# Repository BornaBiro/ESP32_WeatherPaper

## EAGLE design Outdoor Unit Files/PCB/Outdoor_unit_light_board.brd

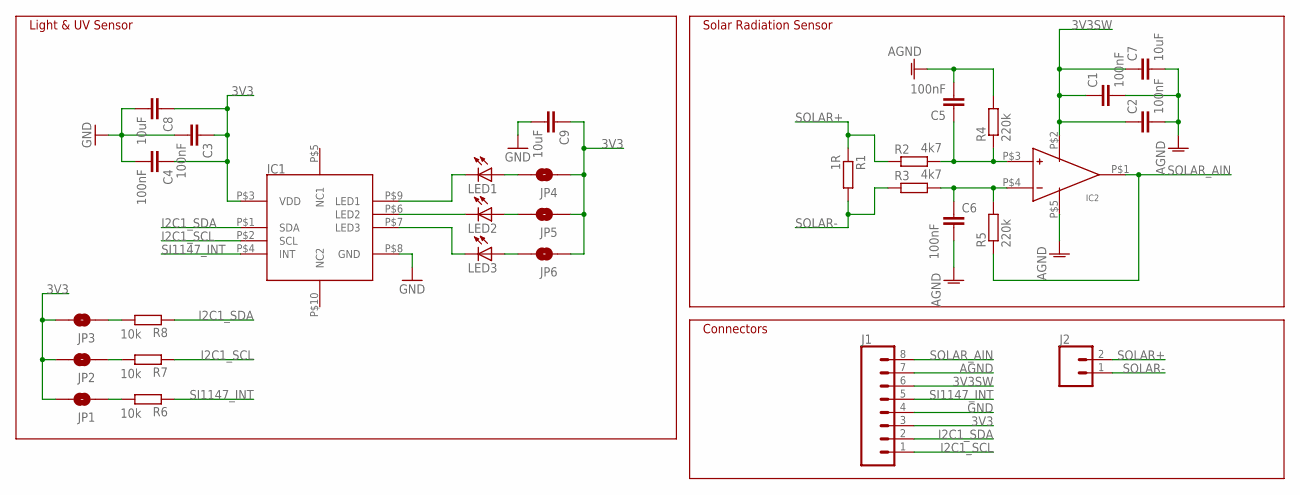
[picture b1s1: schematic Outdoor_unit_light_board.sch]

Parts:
C1, C2, C3, C4, C5, C6: 100nF; C0603K
C7, C8, C9: 10uF; C1206K
IC1: SI1147-A10-GMR; QFN10
IC2: MCP601RT-I/OT; SOT23-5
J1: CONN_08"; 1X08
J2: CONN_02; 1X02
JP1, JP2, JP3, JP4, JP5, JP6: JUMPER-SMT_2_NO_SILK; SMT-JUMPER_2_NO_SILK
LED1, LED2, LED3: LEDCHIPLED_0603; CHIPLED_0603
R1: 1R; R0603
R2, R3: 4k7; R0603
R4, R5: 220k; R0603
R6, R7, R8: 10k; R0603

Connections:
3V3: C3.1, C4.1, C8.1, C9.1, IC1.P$3 (VDD), J1.3, JP1.2, JP2.2, JP3.2, JP4.1, JP5.1, JP6.1
3V3SW: C1.1, C2.1, C7.1, IC2.P$2 (VDD), J1.6
AGND: C1.2, C2.2, C5.2, C6.2, C7.2, IC2.P$5 (VSS), J1.7, R4.2
GND: C3.2, C4.2, C8.2, C9.2, IC1.P$8 (GND), J1.4
I2C1_SCL: IC1.P$2 (SCL), J1.1, R7.1
I2C1_SDA: IC1.P$1 (SDA), J1.2, R8.1
unnamed: IC1.P$6 (LED2), LED2.C
unnamed: C5.1, IC2.P$3 (+IN), R2.2, R4.1
unnamed: C6.1, IC2.P$4 (-IN), R3.2, R5.2
unnamed: IC1.P$7 (LED3), LED3.C
unnamed: IC1.P$9 (LED1), LED1.C
unnamed: JP1.1, R6.2
unnamed: JP4.2, LED1.A
unnamed: JP5.2, LED2.A
unnamed: JP6.2, LED3.A
unnamed: JP2.1, R7.2
unnamed: JP3.1, R8.2
SI1147_INT: IC1.P$4 (INT), J1.5, R6.1
SOLAR+: J2.2, R1.1, R2.1
SOLAR-: J2.1, R1.2, R3.1
SOLAR_AIN: IC2.P$1 (OUT), J1.8, R5.1

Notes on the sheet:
Solar Radiation Sensor
Light & UV Sensor
Connectors

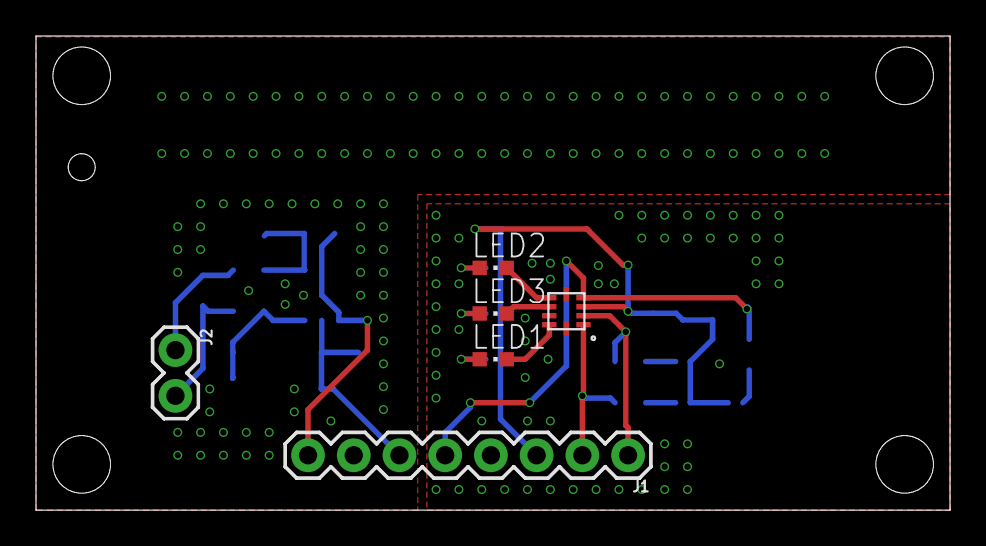
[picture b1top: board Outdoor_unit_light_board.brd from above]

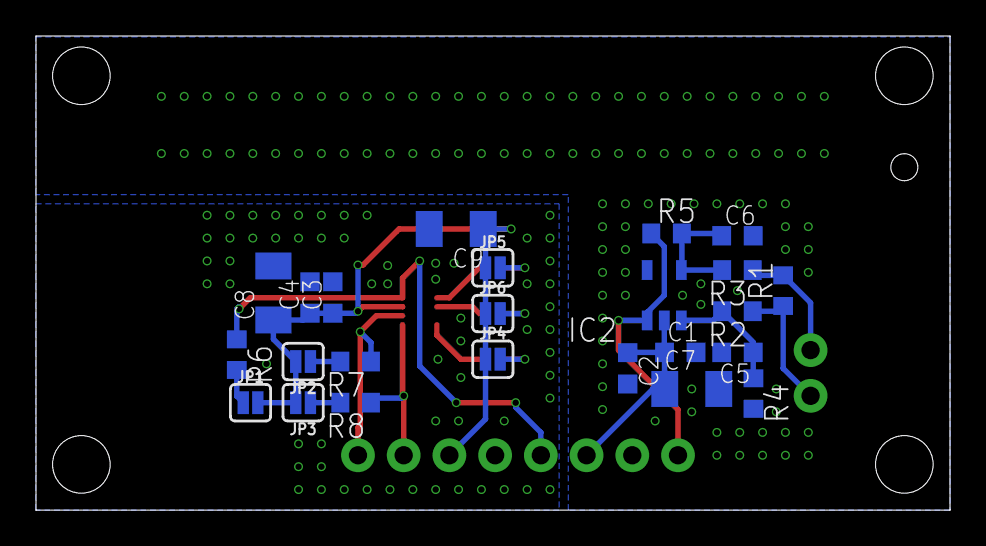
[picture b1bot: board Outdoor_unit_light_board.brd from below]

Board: 2 copper layers, 50.8 x 26.3 mm, 30 parts (24 on the bottom side), 21 nets.

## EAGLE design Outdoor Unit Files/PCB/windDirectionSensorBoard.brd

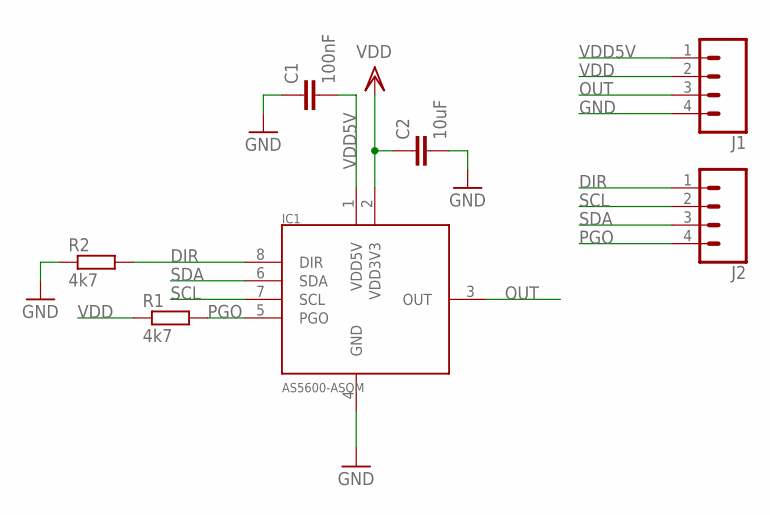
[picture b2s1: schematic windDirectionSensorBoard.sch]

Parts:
C1: 100nF; C0603K
C2: 10uF; C1206K
IC1: AS5600-ASOM; SOIC-8
J1, J2: CONN_04; 1X04
R1, R2: 4k7; R0603

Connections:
DIR: IC1.8 (DIR), J2.1, R2.2
GND: C1.1, C2.2, IC1.4 (GND), J1.4, R2.1
OUT: IC1.3 (OUT), J1.3
PGO: IC1.5 (PGO), J2.4, R1.2
SCL: IC1.7 (SCL), J2.2
SDA: IC1.6 (SDA), J2.3
VDD: C2.1, IC1.2 (VDD3V3), J1.2, R1.1
VDD5V: C1.2, IC1.1 (VDD5V), J1.1

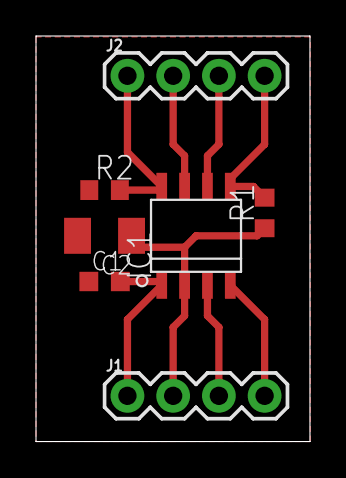
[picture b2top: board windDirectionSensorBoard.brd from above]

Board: 2 copper layers, 15.2 x 22.5 mm, 7 parts (0 on the bottom side), 8 nets.

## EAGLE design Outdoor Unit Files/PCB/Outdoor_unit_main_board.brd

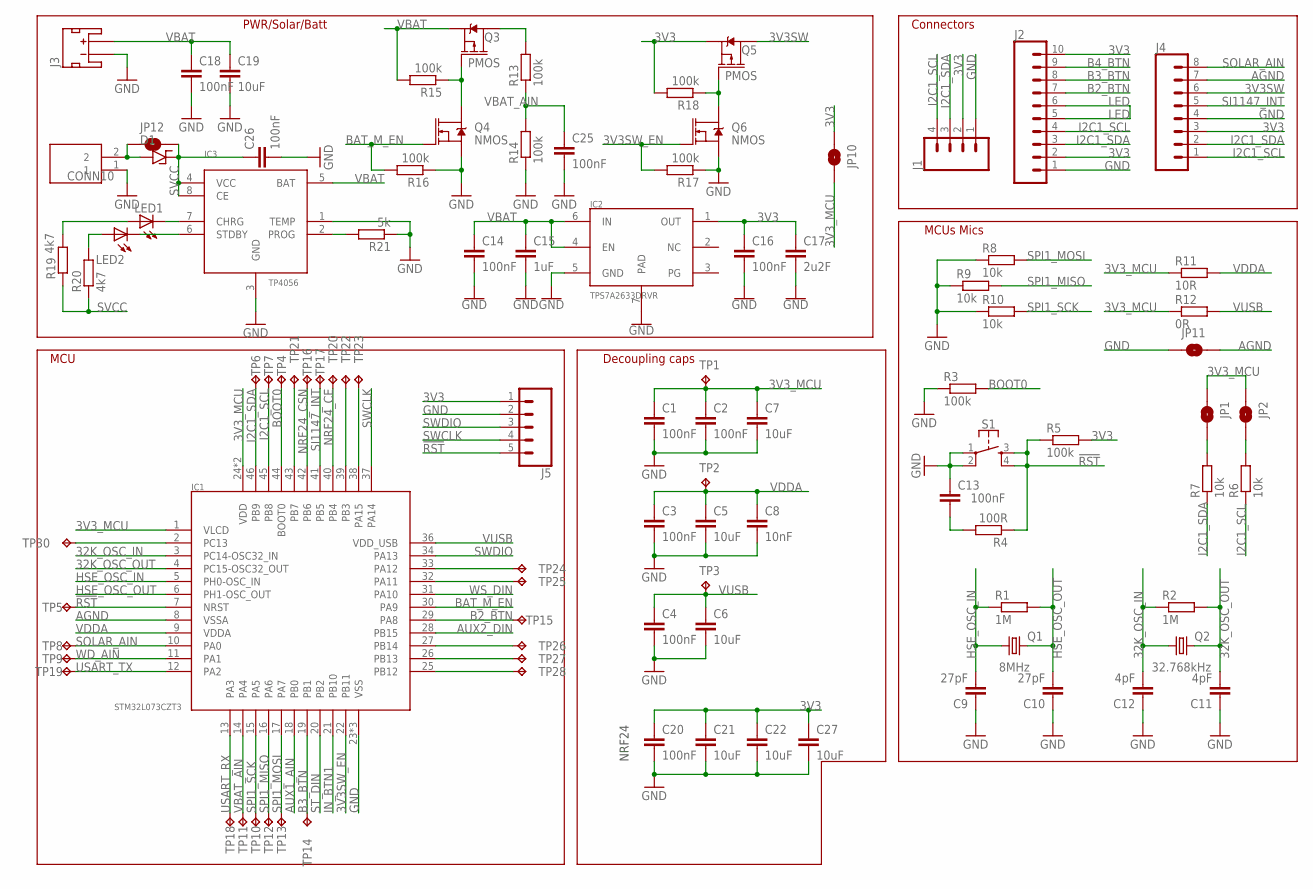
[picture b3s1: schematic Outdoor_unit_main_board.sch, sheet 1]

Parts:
C1, C2, C3, C4, C13, C14, C16, C18, C25, C26: 100nF; C0603K
C5, C6, C7, C19, C21, C22, C27: 10uF; C1206
C8: 10nF; C0603K
C9, C10: 27pF; C0603K
C11, C12: 4pF; C0603K
C15: 1uF; C0603K
C17: 2u2F; C0603K
C20: 100nF; C0603
CONN10: 1X02_SCREW_TERM; ASS_4091_CO
D1: SS24
IC1: STM32L073CZT3; LQFP-48
IC2: TPS7A2633DRVR; WSON-6
IC3: TP4056; SOP-8
J1: CONN_04; 1X04
J2: CONN_10"; 1X10
J3: JST_2MM_MALE; JST-2-SMD
J4: CONN_08"; 1X08
J5: CONN_05; 1X05
JP1, JP2, JP10, JP11, JP12: JUMPER-SMT_2_NO_SILK; SMT-JUMPER_2_NO_SILK
LED1, LED2: LEDCHIP-LED0805; CHIP-LED0805
Q1: 8MHz; HC49/S
Q2: 32.768kHz; TC26V
Q3, Q5: PMOS; SOT23-3
Q4, Q6: NMOS; SOT23-3
R1, R2: 1M; R0603
R3, R5, R13, R14, R15, R16, R17, R18: 100k; R0603
R4: 100R; R0603
R6, R7, R8, R9, R10: 10k; R0603
R11: 10R; R0603
R12: 0R; R0603
R19, R20: 4k7; R0603
R21: 5k; R0603
S1: MOMENTARY-SWITCH-SPST-2-SMD-5.2MM; TACTILE_SWITCH_SMD_5.2MM
TP1, TP2, TP3, TP4, TP5, TP6, TP7, TP8, TP9, TP10, TP11, TP12, TP13, TP14, TP15, TP16, TP17, TP18, TP19, TP20, TP21, TP22, TP23, TP24, TP25, TP26, TP27, TP28, TP30: TPTP15R; TP15R

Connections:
3V3: C16.1, C17.1, C20.1, C21.1, C22.1, C27.1, IC2.1 (OUT), J1.2, J2.2, J2.10, J4.3, J5.1, JP10.1, Q5.2 (S), R5.2, R18.2; also elsewhere on the board
3V3SW: J4.6, Q5.3 (D); also elsewhere on the board
3V3SW_EN: IC1.22 (PB11), Q6.1 (G), R17.2
3V3_MCU: C1.1, C2.1, C7.1, IC1.1 (VLCD), IC1.24 (VDD), IC1.48 (VDD), JP1.1, JP2.1, JP10.2, R11.1, R12.1, TP1.TP
32K_OSC_IN: C12.2, IC1.3 (PC14-OSC32_IN), Q2.1, R2.1
32K_OSC_OUT: C11.2, IC1.4 (PC15-OSC32_OUT), Q2.2, R2.2
!RST: IC1.7 (NRST), J5.5, R4.1, R5.1, S1.3, S1.4, TP5.TP
AGND: IC1.8 (VSSA), J4.7, JP11.2; also elsewhere on the board
AUX1_AIN: IC1.18 (PB0); also elsewhere on the board
AUX2_DIN: IC1.28 (PB15); also elsewhere on the board
B2_BTN: IC1.29 (PA8), J2.7, TP15.TP
B3_BTN: IC1.19 (PB1), J2.8, TP14.TP
B4_BTN: J2.9
BAT_M_EN: IC1.30 (PA9), Q4.1 (G), R16.2
BOOT0: IC1.44 (BOOT0), R3.2, TP4.TP
GND: C1.2, C2.2, C3.2, C4.2, C5.2, C6.2, C7.2, C8.2, C9.1, C10.1, C11.1, C12.1, C13.1, C14.2, C15.2, C16.2, C17.2, C18.2, C19.2, C20.2, C21.2, C22.2, C25.2, C26.2, C27.2, CONN10.1, IC1.23 (VSS), IC1.35 (VSS), IC1.47 (VSS), IC2.5 (GND), IC2.7 (PAD), IC3.1 (TEMP), IC3.3 (GND), J1.1, J2.1, J3.1 (-), J4.4, J5.2, JP11.1, Q4.2 (S), Q6.2 (S), R3.1, R8.1, R9.1, R10.1, R14.1, R16.1, R17.1, R21.1, S1.1, S1.2; also elsewhere on the board
HSE_OSC_IN: C9.2, IC1.5 (PH0-OSC_IN), Q1.1, R1.1
HSE_OSC_OUT: C10.2, IC1.6 (PH1-OSC_OUT), Q1.2, R1.2
I2C1_SCL: IC1.45 (PB8), J1.4, J2.4, J4.1, R6.1, TP7.TP; also elsewhere on the board
I2C1_SDA: IC1.46 (PB9), J1.3, J2.3, J4.2, R7.1, TP6.TP; also elsewhere on the board
IN_BTN1: IC1.21 (PB10); also elsewhere on the board
LED: J2.5, J2.6
unnamed: CONN10.2, D1.A, JP12.1
unnamed: JP1.2, R7.2
unnamed: C13.2, R4.2
unnamed: JP2.2, R6.2
unnamed: IC3.7 (CHRG), LED1.C
unnamed: IC3.6 (STDBY), LED2.C
unnamed: LED2.A, R20.2
unnamed: IC1.33 (PA12), TP24.TP
unnamed: IC1.32 (PA11), TP25.TP
unnamed: IC1.27 (PB14), TP26.TP
unnamed: IC1.26 (PB13), TP27.TP
unnamed: IC1.25 (PB12), TP28.TP
unnamed: IC1.38 (PA15), TP23.TP
unnamed: IC1.39 (PB3), TP22.TP
unnamed: IC1.43 (PB7), TP21.TP
unnamed: IC1.2 (PC13), TP30.TP
unnamed: Q3.3 (D), R13.2
unnamed: LED1.A, R19.2
unnamed: IC3.2 (PROG), R21.2
unnamed: Q3.1 (G), Q4.3 (D), R15.1
unnamed: Q5.1 (G), Q6.3 (D), R18.1
NRF24_CE: IC1.40 (PB4), TP20.TP; also elsewhere on the board
NRF24_CSN: IC1.42 (PB6), TP16.TP; also elsewhere on the board
SI1147_INT: IC1.41 (PB5), J4.5, TP17.TP
SOLAR_AIN: IC1.10 (PA0), J4.8, TP8.TP
SPI1_MISO: IC1.16 (PA6), R9.2, TP12.TP; also elsewhere on the board
SPI1_MOSI: IC1.17 (PA7), R8.2, TP13.TP; also elsewhere on the board
SPI1_SCK: IC1.15 (PA5), R10.2, TP10.TP; also elsewhere on the board
ST_DIN: IC1.20 (PB2); also elsewhere on the board
SVCC: C26.1, D1.C, IC3.4 (VCC), IC3.8 (CE), JP12.2, R19.1, R20.1
SWCLK: IC1.37 (PA14), J5.4
SWDIO: IC1.34 (PA13), J5.3
USART_RX: IC1.13 (PA3), TP18.TP
USART_TX: IC1.12 (PA2), TP19.TP
VBAT: C14.1, C15.1, C18.1, C19.1, IC2.4 (EN), IC2.6 (IN), IC3.5 (BAT), J3.2 (+), Q3.2 (S), R15.2
VBAT_AIN: C25.1, IC1.14 (PA4), R13.1, R14.2, TP11.TP
VDDA: C3.1, C5.1, C8.1, IC1.9 (VDDA), R11.2, TP2.TP
VUSB: C4.1, C6.1, IC1.36 (VDD_USB), R12.2, TP3.TP
WD_AIN: IC1.11 (PA1), TP9.TP; also elsewhere on the board
WS_DIN: IC1.31 (PA10); also elsewhere on the board

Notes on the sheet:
MCU
Decoupling caps
MCUs Mics
NRF24
PWR/Solar/Batt
Connectors

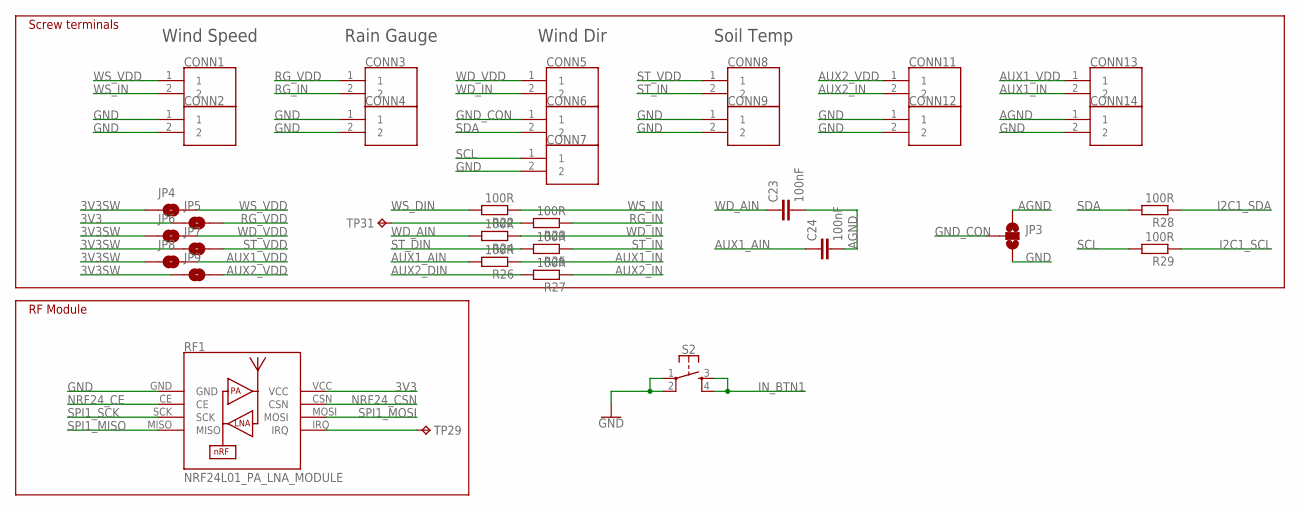
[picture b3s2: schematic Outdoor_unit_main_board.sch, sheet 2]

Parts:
C23, C24: 100nF; C0603K
CONN1, CONN2, CONN3, CONN4, CONN5, CONN6, CONN7, CONN8, CONN9, CONN11, CONN12, CONN13, CONN14: 1X02_SCREW_TERM; ASS_4091_CO
JP3: JUMPER-SMT_3_NO_SILK; SMT-JUMPER_3_NO_SILK
JP4, JP5, JP6, JP7, JP8, JP9: JUMPER-SMT_2_NO_SILK; SMT-JUMPER_2_NO_SILK
R22, R23, R24, R25, R26, R27, R28, R29: 100R; R0603
RF1: NRF24L01_PA_LNA_MODULE; NRF24L01_PA_LNA
S2: MOMENTARY-SWITCH-SPST-2-SMD-5.2MM; TACTILE_SWITCH_SMD_5.2MM
TP29, TP31: TPTP15R; TP15R

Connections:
3V3: JP5.1, RF1.VCC; also elsewhere on the board
3V3SW: JP4.1, JP6.1, JP7.1, JP8.1, JP9.1; also elsewhere on the board
AGND: C23.2, C24.2, CONN14.1, JP3.1; also elsewhere on the board
AUX1_AIN: C24.1, R26.2; also elsewhere on the board
AUX1_IN: CONN13.2, R26.1
AUX1_VDD: CONN13.1, JP8.2
AUX2_DIN: R27.2; also elsewhere on the board
AUX2_IN: CONN11.2, R27.1
AUX2_VDD: CONN11.1, JP9.2
GND: CONN2.1, CONN2.2, CONN4.1, CONN4.2, CONN7.2, CONN9.1, CONN9.2, CONN12.1, CONN12.2, CONN14.2, JP3.3, RF1.GND, S2.1, S2.2; also elsewhere on the board
GND_CON: CONN6.1, JP3.2
I2C1_SCL: R29.1; also elsewhere on the board
I2C1_SDA: R28.1; also elsewhere on the board
IN_BTN1: S2.3, S2.4; also elsewhere on the board
unnamed: RF1.IRQ, TP29.TP
unnamed: R23.2, TP31.TP
NRF24_CE: RF1.CE; also elsewhere on the board
NRF24_CSN: RF1.CSN; also elsewhere on the board
RG_IN: CONN3.2, R23.1
RG_VDD: CONN3.1, JP5.2
SCL: CONN7.1, R29.2
SDA: CONN6.2, R28.2
SPI1_MISO: RF1.MISO; also elsewhere on the board
SPI1_MOSI: RF1.MOSI; also elsewhere on the board
SPI1_SCK: RF1.SCK; also elsewhere on the board
ST_DIN: R25.2; also elsewhere on the board
ST_IN: CONN8.2, R25.1
ST_VDD: CONN8.1, JP7.2
WD_AIN: C23.1, R24.2; also elsewhere on the board
WD_IN: CONN5.2, R24.1
WD_VDD: CONN5.1, JP6.2
WS_DIN: R22.2; also elsewhere on the board
WS_IN: CONN1.2, R22.1
WS_VDD: CONN1.1, JP4.2

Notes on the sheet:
Wind Speed
Rain Gauge
Wind Dir
Soil Temp
Screw terminals
RF Module

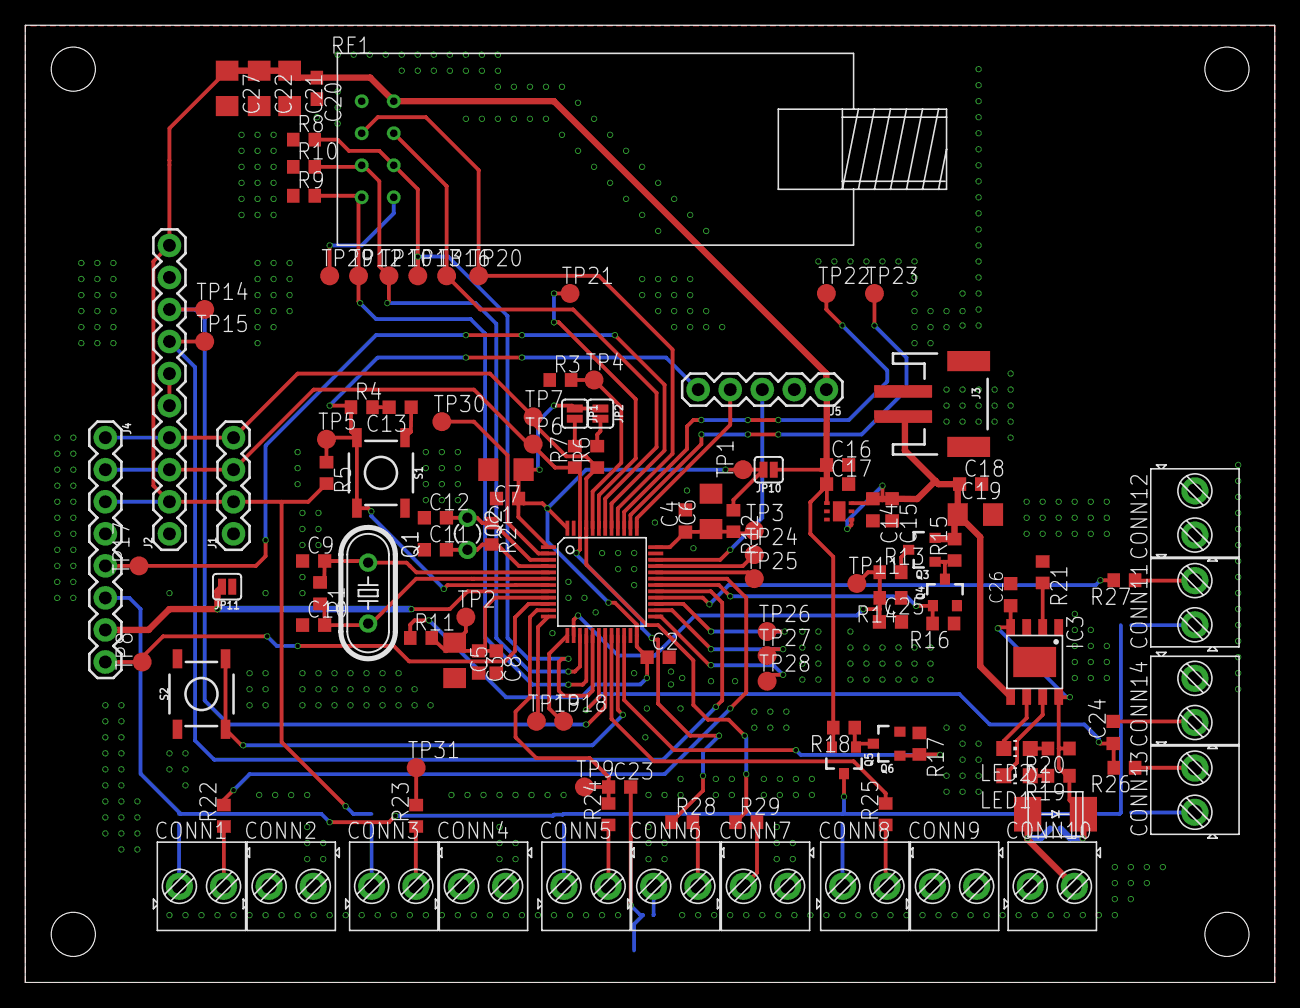
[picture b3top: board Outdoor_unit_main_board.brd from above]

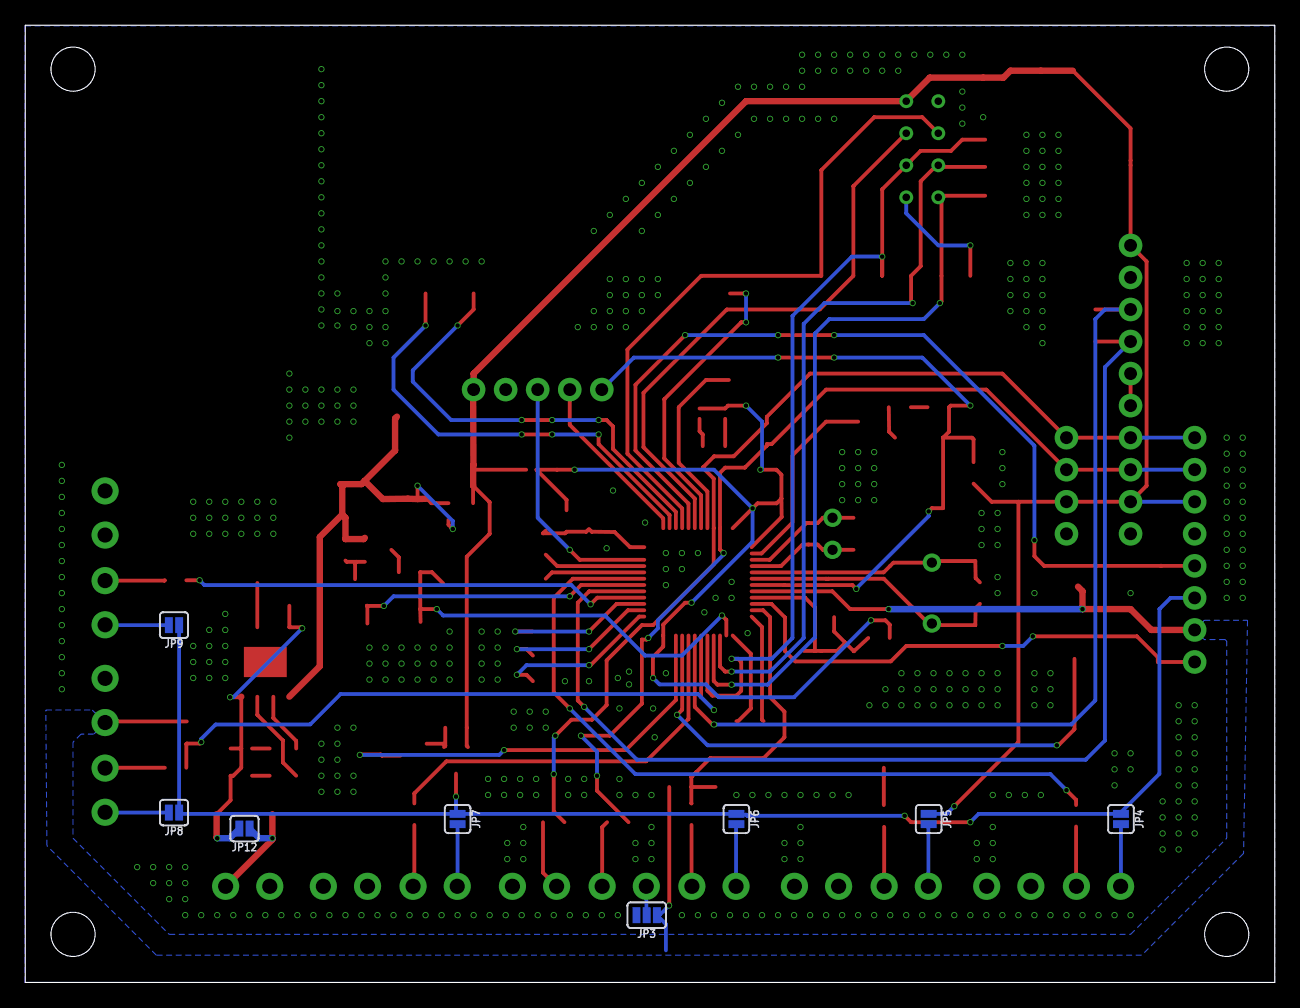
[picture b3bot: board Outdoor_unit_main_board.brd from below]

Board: 2 copper layers, 99.0 x 75.9 mm, 133 parts (8 on the bottom side), 78 nets.

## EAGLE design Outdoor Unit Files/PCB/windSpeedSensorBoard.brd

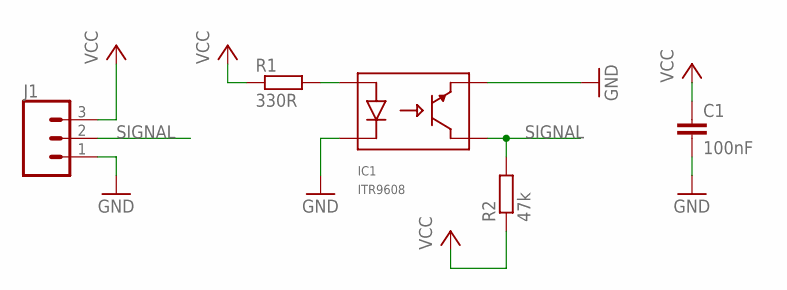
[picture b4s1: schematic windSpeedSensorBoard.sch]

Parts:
C1: 100nF; C0603K
IC1: ITR9608
J1: CONN_03; 1X03
R1: 330R; R0603
R2: 47k; R0603

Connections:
GND: C1.2, IC1.E, IC1.K, J1.1
unnamed: IC1.A, R1.2
SIGNAL: IC1.C, J1.2, R2.2
VCC: C1.1, J1.3, R1.1, R2.1

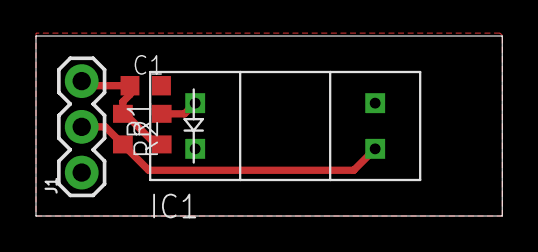
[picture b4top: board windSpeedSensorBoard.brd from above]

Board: 2 copper layers, 25.9 x 10.0 mm, 5 parts (0 on the bottom side), 4 nets.

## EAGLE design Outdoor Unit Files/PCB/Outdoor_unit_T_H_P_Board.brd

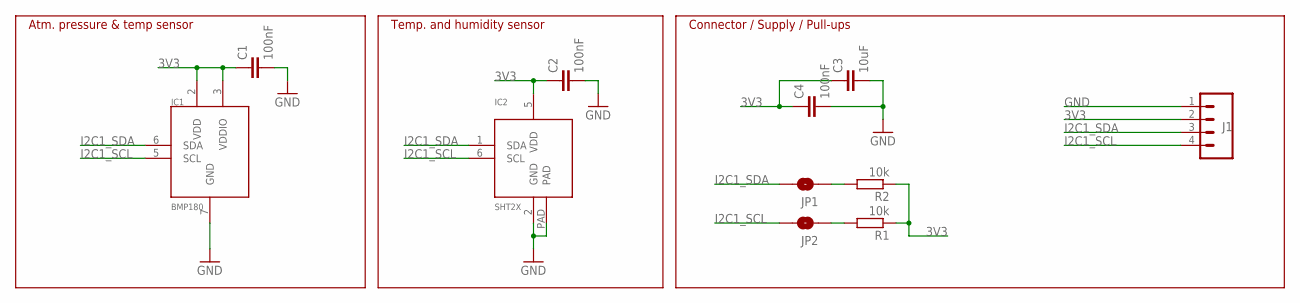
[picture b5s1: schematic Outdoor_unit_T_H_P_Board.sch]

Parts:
C1, C2, C4: 100nF; C0603K
C3: 10uF; C1206K
IC1: BMP180
IC2: SHT2X
J1: CONN_04; 1X04
JP1, JP2: JUMPER-SMT_2_NO_SILK; SMT-JUMPER_2_NO_SILK
R1, R2: 10k; R0603

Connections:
3V3: C1.1, C2.1, C3.1, C4.1, IC1.2 (VDD), IC1.3 (VDDIO), IC2.5 (VDD), J1.2, R1.1, R2.1
GND: C1.2, C2.2, C3.2, C4.2, IC1.7 (GND), IC2.2 (GND), IC2.PAD, J1.1
I2C1_SCL: IC1.5 (SCL), IC2.6 (SCL), J1.4, JP2.2
I2C1_SDA: IC1.6 (SDA), IC2.1 (SDA), J1.3, JP1.2
unnamed: JP2.1, R1.2
unnamed: JP1.1, R2.2

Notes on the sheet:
Atm. pressure & temp sensor
Temp. and humidity sensor
Connector / Supply / Pull-ups

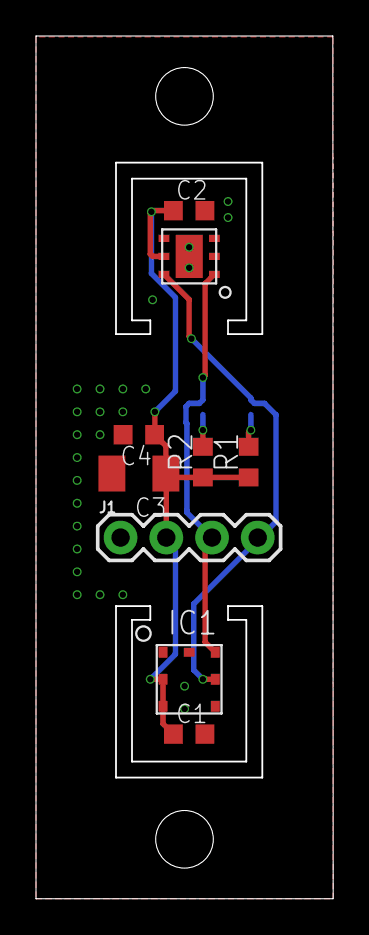
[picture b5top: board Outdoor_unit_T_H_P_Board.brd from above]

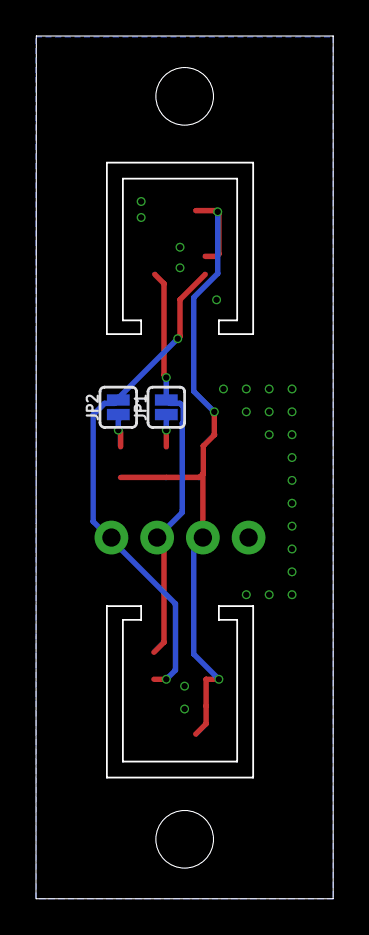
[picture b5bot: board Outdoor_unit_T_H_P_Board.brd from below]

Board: 2 copper layers, 16.5 x 47.9 mm, 11 parts (2 on the bottom side), 6 nets.

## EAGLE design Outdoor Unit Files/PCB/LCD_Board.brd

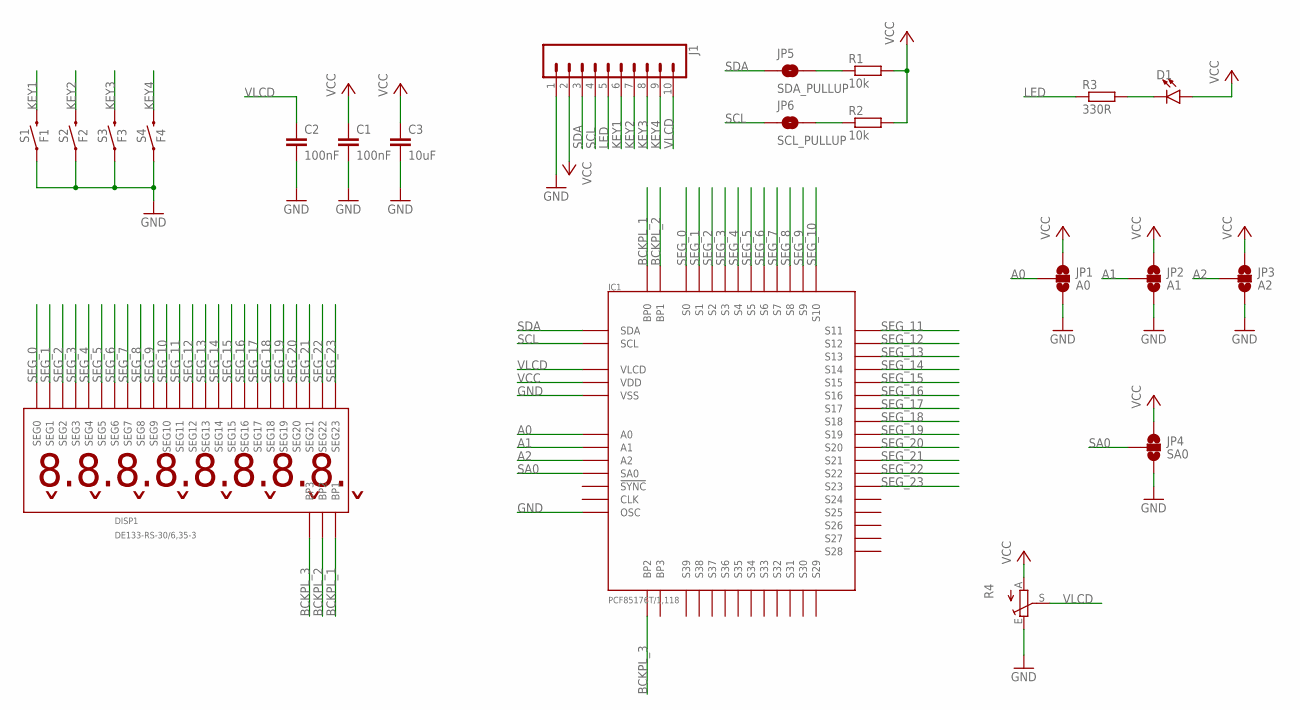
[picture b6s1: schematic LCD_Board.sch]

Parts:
C1, C2: 100nF; C0603K
C3: 10uF; C1206K
D1: LED3MM; LED_3MM
DISP1: DE133-RS-30/6.35-3
IC1: PCF85176T/1,118; TSSOP56
J1: CONN_10"; 1X10
JP1: A0; SMT-JUMPER_3_NO_SILK
JP2: A1; SMT-JUMPER_3_NO_SILK
JP3: A2; SMT-JUMPER_3_NO_SILK
JP4: SA0; SMT-JUMPER_3_NO_SILK
JP5: SDA_PULLUP; SMT-JUMPER_2_NO_SILK
JP6: SCL_PULLUP; SMT-JUMPER_2_NO_SILK
R1, R2: 10k; R0603
R3: 330R; R0603
R4: TRIM_EU-CA6V; CA6V
S1: F1; TACTILE_SWITCH_SMD_5.2MM
S2: F2; TACTILE_SWITCH_SMD_5.2MM
S3: F3; TACTILE_SWITCH_SMD_5.2MM
S4: F4; TACTILE_SWITCH_SMD_5.2MM

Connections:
A0: IC1.P$50 (A0), JP1.2
A1: IC1.P$51 (A1), JP2.2
A2: IC1.P$52 (A2), JP3.2
BCKPL_1: DISP1.P$25 (BP1), DISP1.P$30 (BP1), IC1.P$56 (BP0)
BCKPL_2: DISP1.P$26 (BP2), DISP1.P$29 (BP2), IC1.P$2 (BP1)
BCKPL_3: DISP1.P$27 (BP3), DISP1.P$28 (BP3), IC1.P$1 (BP2)
GND: C1.2, C2.2, C3.2, IC1.P$49 (OSC), IC1.P$54 (VSS), J1.1, JP1.3, JP2.3, JP3.3, JP4.3, R4.E, S1.1, S2.1, S3.1, S4.1
KEY1: J1.6, S1.3 (2)
KEY2: J1.7, S2.3 (2)
KEY3: J1.8, S3.3 (2)
KEY4: J1.9, S4.3 (2)
LED: J1.5, R3.1
unnamed: JP5.2, R1.1
unnamed: JP6.2, R2.1
unnamed: D1.K (C), R3.2
SA0: IC1.P$53 (SA0), JP4.2
SCL: IC1.P$45 (SCL), J1.4, JP6.1
SDA: IC1.P$44 (SDA), J1.3, JP5.1
SEG_0: DISP1.P$1 (SEG0), IC1.P$4 (S0)
SEG_1: DISP1.P$2 (SEG1), IC1.P$5 (S1)
SEG_2: DISP1.P$3 (SEG2), IC1.P$6 (S2)
SEG_3: DISP1.P$4 (SEG3), IC1.P$7 (S3)
SEG_4: DISP1.P$5 (SEG4), IC1.P$8 (S4)
SEG_5: DISP1.P$6 (SEG5), IC1.P$9 (S5)
SEG_6: DISP1.P$7 (SEG6), IC1.P$10 (S6)
SEG_7: DISP1.P$8 (SEG7), IC1.P$11 (S7)
SEG_8: DISP1.P$9 (SEG8), IC1.P$12 (S8)
SEG_9: DISP1.P$10 (SEG9), IC1.P$13 (S9)
SEG_10: DISP1.P$11 (SEG10), IC1.P$14 (S10)
SEG_11: DISP1.P$12 (SEG11), IC1.P$15 (S11)
SEG_12: DISP1.P$13 (SEG12), IC1.P$16 (S12)
SEG_13: DISP1.P$14 (SEG13), IC1.P$17 (S13)
SEG_14: DISP1.P$15 (SEG14), IC1.P$18 (S14)
SEG_15: DISP1.P$16 (SEG15), IC1.P$19 (S15)
SEG_16: DISP1.P$17 (SEG16), IC1.P$20 (S16)
SEG_17: DISP1.P$18 (SEG17), IC1.P$21 (S17)
SEG_18: DISP1.P$19 (SEG18), IC1.P$22 (S18)
SEG_19: DISP1.P$20 (SEG19), IC1.P$23 (S19)
SEG_20: DISP1.P$21 (SEG20), IC1.P$24 (S20)
SEG_21: DISP1.P$22 (SEG21), IC1.P$25 (S21)
SEG_22: DISP1.P$23 (SEG22), IC1.P$26 (S22)
SEG_23: DISP1.P$24 (SEG23), IC1.P$27 (S23)
VCC: C1.1, C3.1, D1.A, IC1.P$48 (VDD), J1.2, JP1.1, JP2.1, JP3.1, JP4.1, R1.2, R2.2, R4.A
VLCD: C2.1, IC1.P$55 (VLCD), J1.10, R4.S

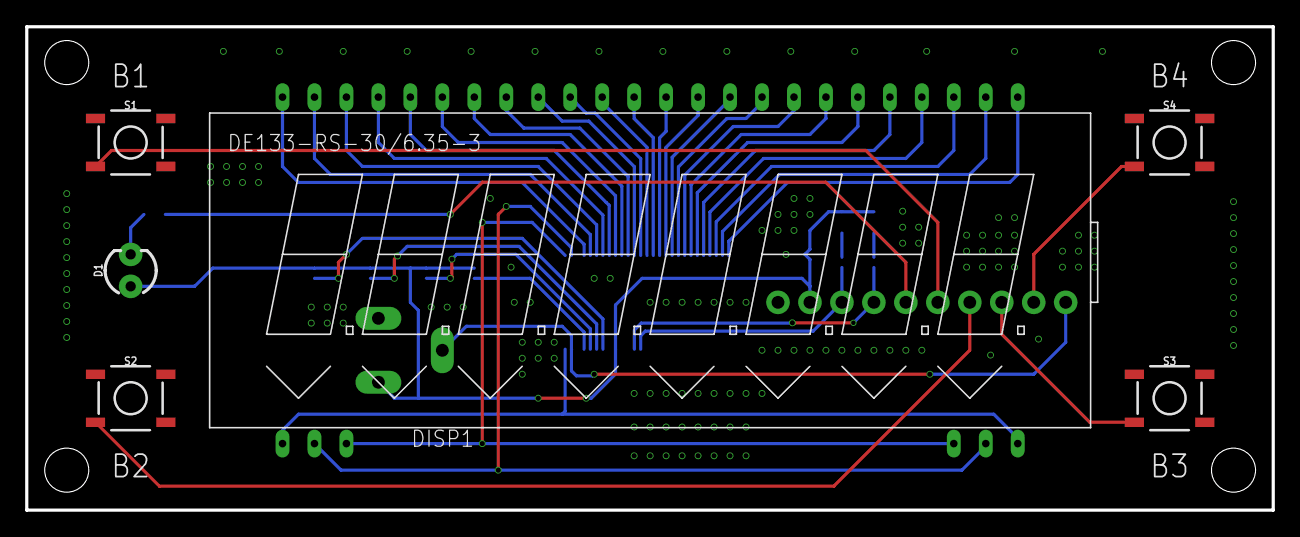
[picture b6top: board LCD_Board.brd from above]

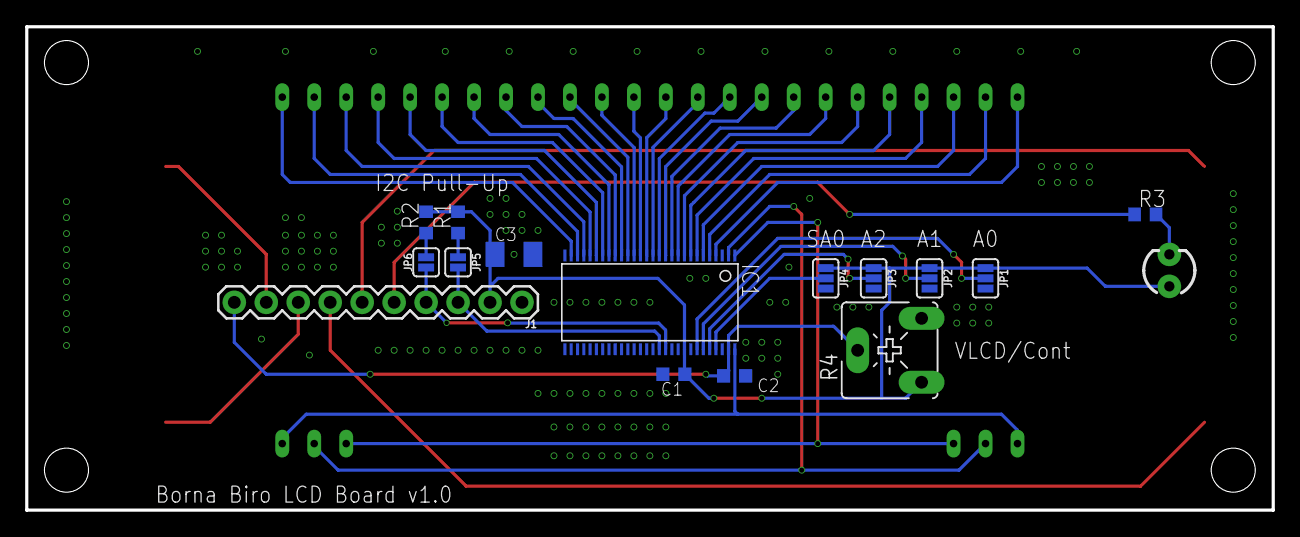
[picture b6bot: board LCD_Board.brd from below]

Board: 2 copper layers, 99.0 x 38.4 mm, 21 parts (15 on the bottom side), 44 nets.

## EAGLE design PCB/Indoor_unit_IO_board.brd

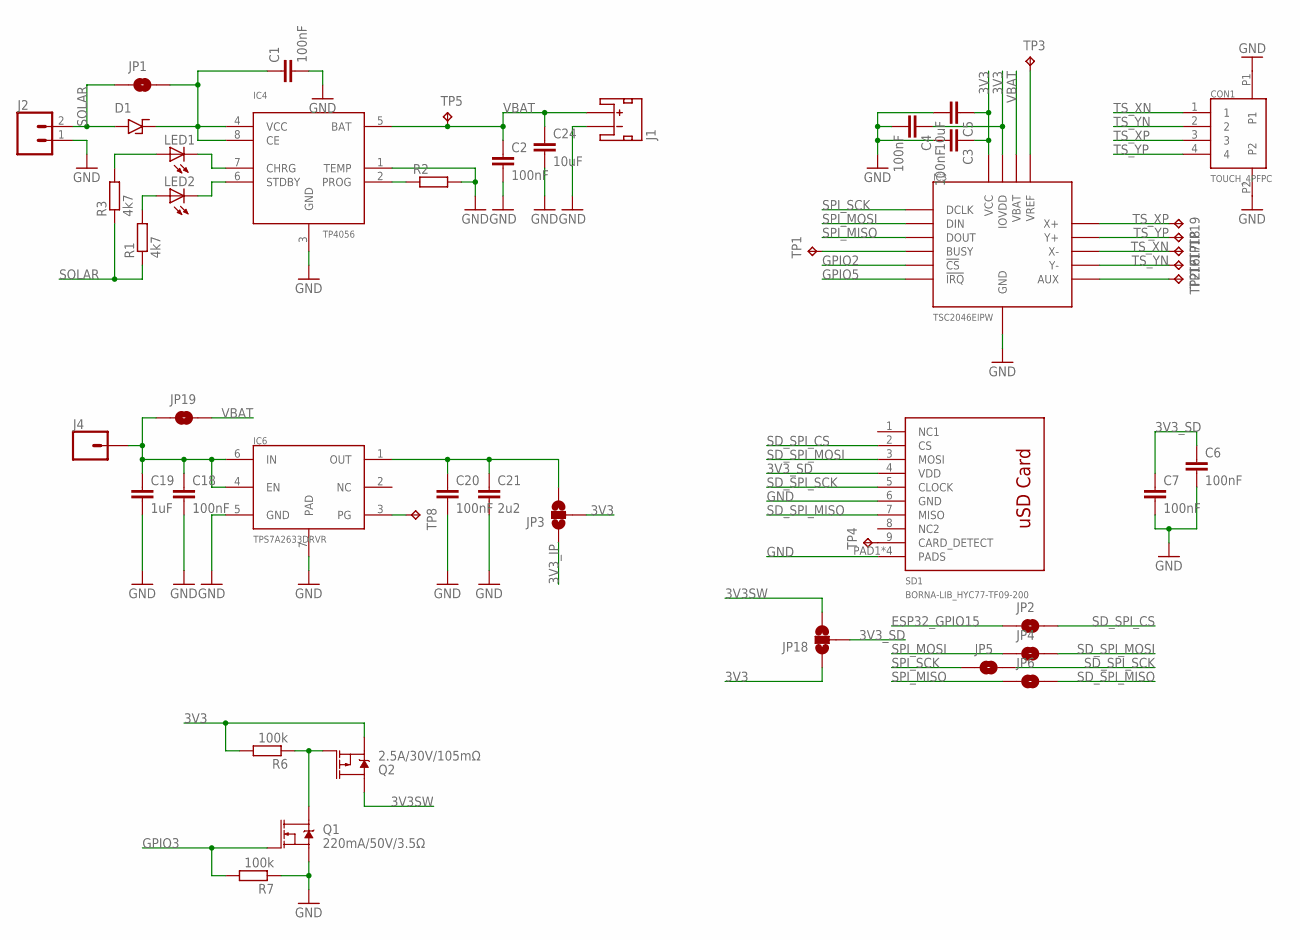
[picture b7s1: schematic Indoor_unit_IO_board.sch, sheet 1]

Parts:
C1, C2, C3, C4, C6, C7, C18, C20: 100nF; C0603K
C5, C24: 10uF; C1206K
C19: 1uF; C0603K
C21: 2u2; C0603K
CON1: TOUCH_4PFPC
D1: SS24
IC3: TSC2046EIPW; TSSOP16
IC4: TP4056; SOP-8
IC6: TPS7A2633DRVR; WSON-6
J1: JST_2MM_MALE; JST-2-SMD
J2: CONN_02; 1X02
J4: CONN_01; 1X01
JP1, JP2, JP4, JP5, JP6, JP19: JUMPER-SMT_2_NO_SILK; SMT-JUMPER_2_NO_SILK
JP3, JP18: JUMPER-SMT_3_NO_SILK; SMT-JUMPER_3_NO_SILK
LED1, LED2: LEDCHIPLED_0603; CHIPLED_0603
Q1: 220mA/50V/3.5Ω; SOT23-3
Q2: 2.5A/30V/105mΩ; SOT23-3
R1, R3: 4k7; R0603
R2: R-EU_R0603; R0603
R6, R7: 100k; R0603
SD1: BORNA-LIB_HYC77-TF09-200; BORNA-LIB_MICROSD_HOLDER
TP1, TP2, TP3, TP4, TP5, TP8, TP16, TP17, TP18, TP19: TPTP15R; TP15R

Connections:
3V3: C3.1, C4.1, C5.1, IC3.P1 (VCC), IC3.P10 (IOVDD), JP3.2, JP18.1, Q2.2 (S), R6.2; also elsewhere on the board
3V3SW: JP18.3, Q2.3 (D); also elsewhere on the board
3V3_IP: JP3.1; also elsewhere on the board
3V3_SD: C6.1, C7.1, JP18.2, SD1.4 (VDD)
ESP32_GPIO15: JP2.1; also elsewhere on the board
GND: C1.2, C2.2, C3.2, C4.2, C5.2, C6.2, C7.2, C18.2, C19.2, C20.2, C21.2, C24.2, CON1.P1, CON1.P2, IC3.P6 (GND), IC4.1 (TEMP), IC4.3 (GND), IC6.5 (GND), IC6.7 (PAD), J1.1 (-), J2.1, Q1.2 (S), R2.2, R7.1, SD1.6 (GND), SD1.PAD1 (PADS), SD1.PAD2 (PADS), SD1.PAD3 (PADS), SD1.PAD4 (PADS); also elsewhere on the board
GPIO2: IC3.P15 (!CS); also elsewhere on the board
GPIO3: Q1.1 (G), R7.2; also elsewhere on the board
GPIO5: IC3.P11 (!IRQ); also elsewhere on the board
unnamed: C18.1, C19.1, IC6.4 (EN), IC6.6 (IN), J4.1, JP19.1
unnamed: C1.1, D1.C, IC4.4 (VCC), IC4.8 (CE), JP1.2
unnamed: IC4.7 (CHRG), LED1.C
unnamed: IC4.6 (STDBY), LED2.C
unnamed: IC4.2 (PROG), R2.1
unnamed: LED1.A, R3.2
unnamed: LED2.A, R1.2
unnamed: IC6.3 (PG), TP8.TP
unnamed: IC3.P8 (AUX), TP2.TP
unnamed: IC3.P9 (VREF), TP3.TP
unnamed: SD1.9 (CARD_DETECT), TP4.TP
unnamed: C20.1, C21.1, IC6.1 (OUT), JP3.3
unnamed: Q1.3 (D), Q2.1 (G), R6.1
unnamed: IC3.P13 (BUSY), TP1.TP
SD_SPI_CS: JP2.2, SD1.2 (CS)
SD_SPI_MISO: JP6.2, SD1.7 (MISO)
SD_SPI_MOSI: JP4.2, SD1.3 (MOSI)
SD_SPI_SCK: JP5.2, SD1.5 (CLOCK)
SOLAR: D1.A, J2.2, JP1.1, R1.1, R3.1
SPI_MISO: IC3.P12 (DOUT), JP6.1; also elsewhere on the board
SPI_MOSI: IC3.P14 (DIN), JP4.1; also elsewhere on the board
SPI_SCK: IC3.P16 (DCLK), JP5.1; also elsewhere on the board
TS_XN: CON1.1, IC3.P4 (X-), TP17.TP
TS_XP: CON1.3, IC3.P2 (X+), TP19.TP
TS_YN: CON1.2, IC3.P5 (Y-), TP16.TP
TS_YP: CON1.4, IC3.P3 (Y+), TP18.TP
VBAT: C2.1, C24.1, IC3.P7 (VBAT), IC4.5 (BAT), J1.2 (+), JP19.2, TP5.TP

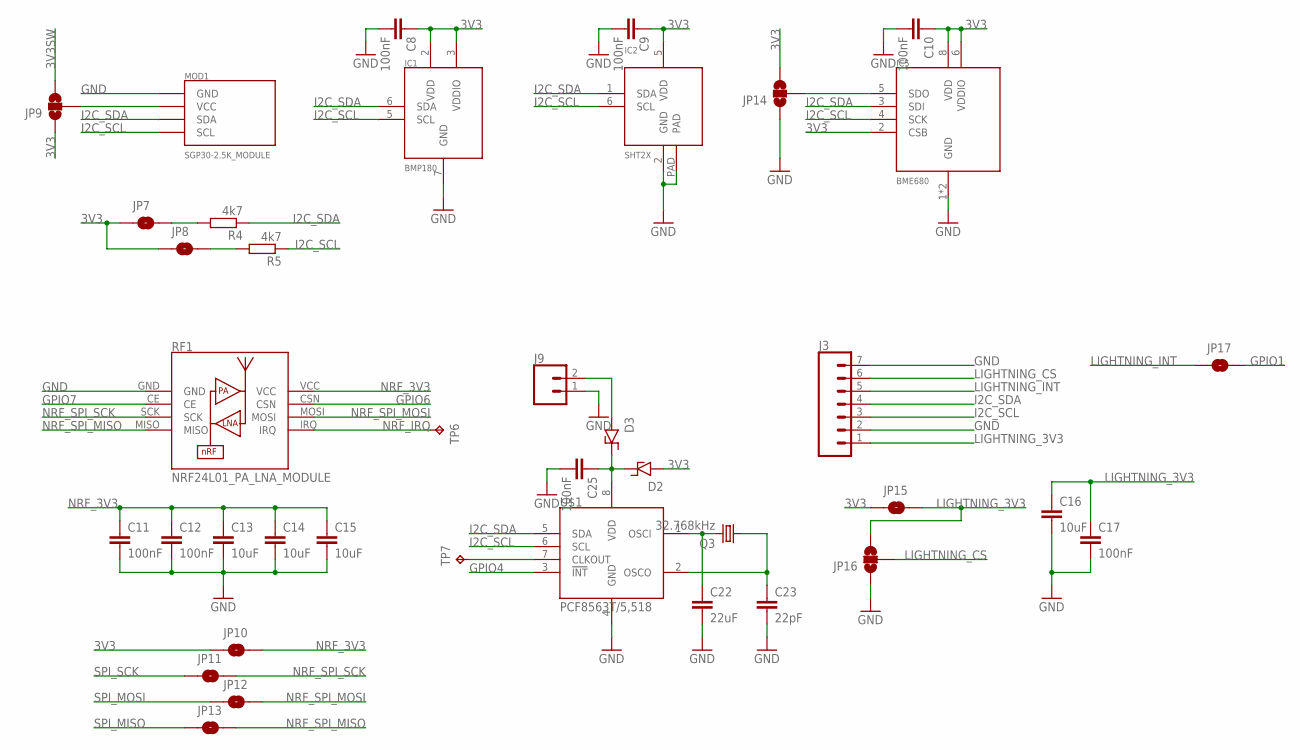
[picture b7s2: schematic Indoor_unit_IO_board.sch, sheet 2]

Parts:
C8, C9, C10, C11, C12, C17, C25: 100nF; C0603K
C13, C14, C15, C16: 10uF; C1206K
C22: 22uF; C0603K
C23: 22pF; C0603K
D2, D3: SS24
IC1: BMP180
IC2: SHT2X
IC5: BME680
J3: CONN_07; 1X07
J9: CONN_02; 1X02
JP7, JP8, JP10, JP11, JP12, JP13, JP15, JP17: JUMPER-SMT_2_NO_SILK; SMT-JUMPER_2_NO_SILK
JP9, JP14, JP16: JUMPER-SMT_3_NO_SILK; SMT-JUMPER_3_NO_SILK
MOD1: SGP30_ERAD_MODULE
Q3: 32.768kHz; TC26H
R4, R5: 4k7; R0603
RF1: NRF24L01_PA_LNA_MODULE; NRF24L01_PA_LNA
TP6, TP7: TPTP15R; TP15R
U$1: PCF8563T/5,518; SOIC-8

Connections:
3V3: C8.1, C9.1, C10.1, D2.A, IC1.2 (VDD), IC1.3 (VDDIO), IC2.5 (VDD), IC5.2 (CSB), IC5.6 (VDDIO), IC5.8 (VDD), JP7.1, JP8.1, JP9.1, JP10.1, JP14.3, JP15.1; also elsewhere on the board
3V3SW: JP9.3; also elsewhere on the board
GND: C8.2, C9.2, C10.2, C11.2, C12.2, C13.2, C14.2, C15.2, C16.2, C17.2, C22.2, C23.2, C25.2, IC1.7 (GND), IC2.2 (GND), IC2.PAD, IC5.1 (GND), IC5.7 (GND), J3.2, J3.7, J9.1, JP14.1, JP16.1, MOD1.GND, RF1.GND, U$1.4 (GND); also elsewhere on the board
GPIO1: JP17.2; also elsewhere on the board
GPIO4: U$1.3 (!INT); also elsewhere on the board
GPIO6: RF1.CSN; also elsewhere on the board
GPIO7: RF1.CE; also elsewhere on the board
I2C_SCL: IC1.5 (SCL), IC2.6 (SCL), IC5.4 (SCK), J3.3, MOD1.SCL, R5.1, U$1.6 (SCL); also elsewhere on the board
I2C_SDA: IC1.6 (SDA), IC2.1 (SDA), IC5.3 (SDI), J3.4, MOD1.SDA, R4.1, U$1.5 (SDA); also elsewhere on the board
LIGHTNING_3V3: C16.1, C17.1, J3.1, JP15.2, JP16.3
LIGHTNING_CS: J3.6, JP16.2
LIGHTNING_INT: J3.5, JP17.1
unnamed: JP9.2, MOD1.VCC
unnamed: IC5.5 (SDO), JP14.2
unnamed: C25.1, D2.C, D3.C, U$1.8 (VDD)
unnamed: JP7.2, R4.2
unnamed: JP8.2, R5.2
unnamed: TP7.TP, U$1.7 (CLKOUT)
unnamed: C22.1, Q3.2, U$1.1 (OSCI)
unnamed: C23.1, Q3.1, U$1.2 (OSCO)
unnamed: D3.A, J9.2
NRF_3V3: C11.1, C12.1, C13.1, C14.1, C15.1, JP10.2, RF1.VCC
NRF_IRQ: RF1.IRQ, TP6.TP
NRF_SPI_MISO: JP13.2, RF1.MISO
NRF_SPI_MOSI: JP12.2, RF1.MOSI
NRF_SPI_SCK: JP11.2, RF1.SCK
SPI_MISO: JP13.1; also elsewhere on the board
SPI_MOSI: JP12.1; also elsewhere on the board
SPI_SCK: JP11.1; also elsewhere on the board

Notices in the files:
parts and their libraries:
SparkFun-Switches: Licensing: Creative Commons ShareAlike 4.0 International - https://creativecommons.org/licenses/by-sa/4.0
